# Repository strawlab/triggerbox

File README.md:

# triggerbox - camera triggering for synchronized multi-camera setups

## Principle of operation

Cameras trigger inputs are connected to pin D9 on an Arduino. (Optionally, a
buffer amplifier can be used. See below for why this may be a good idea.) This
is used to generate a digital pulse which triggers image acquisition on cameras.
Furthermore, a host PC communicates with the Arduino to build a live model of
the clocks on both systems and allows very precise (sub-millisecond)
determination of the timing of trigger pulses from the Arduino. This allows
precise timing information to be taken from the resulting acquired image frames.

## Required hardware:

The minimal required hardware is this:

 - Arduino Nano A000005 (later models WILL NOT WORK).

If using the minimal hardware, you will need to connect pin D9 to the trigger
inputs of your camera directly.

## Optional buffer amplified and circuit board:

For additional robustness for multi-camera setups, particularly those that have
an opto-coupled trigger input which accordingly draws substantially more
current, you will want a buffer amplifier to trigger more cameras. In the
`hardware_v1` and `hardware_v2` directories are the PCB layouts, schematics, and enclosure of the triggerbox.
- Hardware_v1: BNC outputs for triggering only
- Hardware_v2: 4-pin terminal block ouputs for triggering and powering the cameras via external powersource.

## Firmware Build and Install

This firmware can be compiled and installed with the Arduino IDE or at
the command line.

### Option 1: Compiling and Uploading using the Arduino IDE

The file `triggerbox.ino` can be opened directly in the [Arduino
IDE](http://arduino.cc/en/main/software). Set your board to Arduino Nano
("Tools"->"Board"->"Arduino Nano"). Set your port ("Tools"->"Port") correctly,
which depends on your specific computer setup. Then click the "Upload" button.

### Option 2: Command-line Compiling and Uploading using Arduino CLI

To build this firmware for an Arduino Nano on Ubuntu linux, do the following
steps.

Install the required software:

Intall [Arduino CLI](https://arduino.github.io/arduino-cli/latest/), then:

    arduino-cli core update-index
    arduino-cli core install arduino:avr

Compile the firmware

    arduino-cli compile --fqbn arduino:avr:nano

Upload the firmware

    # Note the port `/dev/ttyUSB0` may be different on your computer. In Windows,
    # it will be something like `COM4`.
    arduino-cli upload --port /dev/ttyUSB0 --fqbn arduino:avr:nano

## Testing with host PC

Run the standalone demo program on your host PC. 

 * Prerequisite 1: install [rust](https://rustup.rs/).
 * Prerequisite 2 (linux only): make sure you are in the `dialout` group (or
   whichever group owns the device file - `/dev/ttyUSB0` in the example below):
   ```sudo adduser `whoami` dialout```. 

The demo can be run like this:

    cd braid-triggerbox-rs
    # You may need to change the device path from `/dev/ttyUSB0` in this example.
    # On Windows, this will be something like `COM4` instead of `/dev/ttyUSB0`.
    cargo run -- --device /dev/ttyUSB0 --fps 100
    
If successful, the output will look like:

```
Requested 100 fps, using 100 fps
Connecting to trigger device ..
got new time model: None
.. connected.
got new time model: Some(ClockModel { gain: 0.009991053259000182, offset: 1642089273.653188, residuals: 0.00008373855939680652, n_measurements: 5 })
got new time model: Some(ClockModel { gain: 0.009990740683861077, offset: 1642089273.65347, residuals: 0.00008408054048913982, n_measurements: 6 })
got new time model: Some(ClockModel { gain: 0.009990941849537194, offset: 1642089273.6532729, residuals: 0.00008470585419217969, n_measurements: 7 })
got new time model: Some(ClockModel { gain: 0.0099910874851048, offset: 1642089273.6531227, residuals: 0.00008554253827242064, n_measurements: 8 })
got new time model: Some(ClockModel { gain: 0.009991202969104052, offset: 1642089273.652988, residuals: 0.0000863512614728279, n_measurements: 9 })
got new time model: Some(ClockModel { gain: 0.009991223458200693, offset: 1642089273.652963, residuals: 0.00008639545796995662, n_measurements: 10 })
got new time model: Some(ClockModel { gain: 0.009991292201448232, offset: 1642089273.6528616, residuals: 0.00008692377247143668, n_measurements: 11 })
got new time model: Some(ClockModel { gain: 0.009991496510338038, offset: 1642089273.6525416, residuals: 0.00009343214287582668, n_measurements: 12 })
```

## License

Apache 2.0 or MIT at your choice. See `LICENSE-APACHE` and `LICENSE-MIT`.

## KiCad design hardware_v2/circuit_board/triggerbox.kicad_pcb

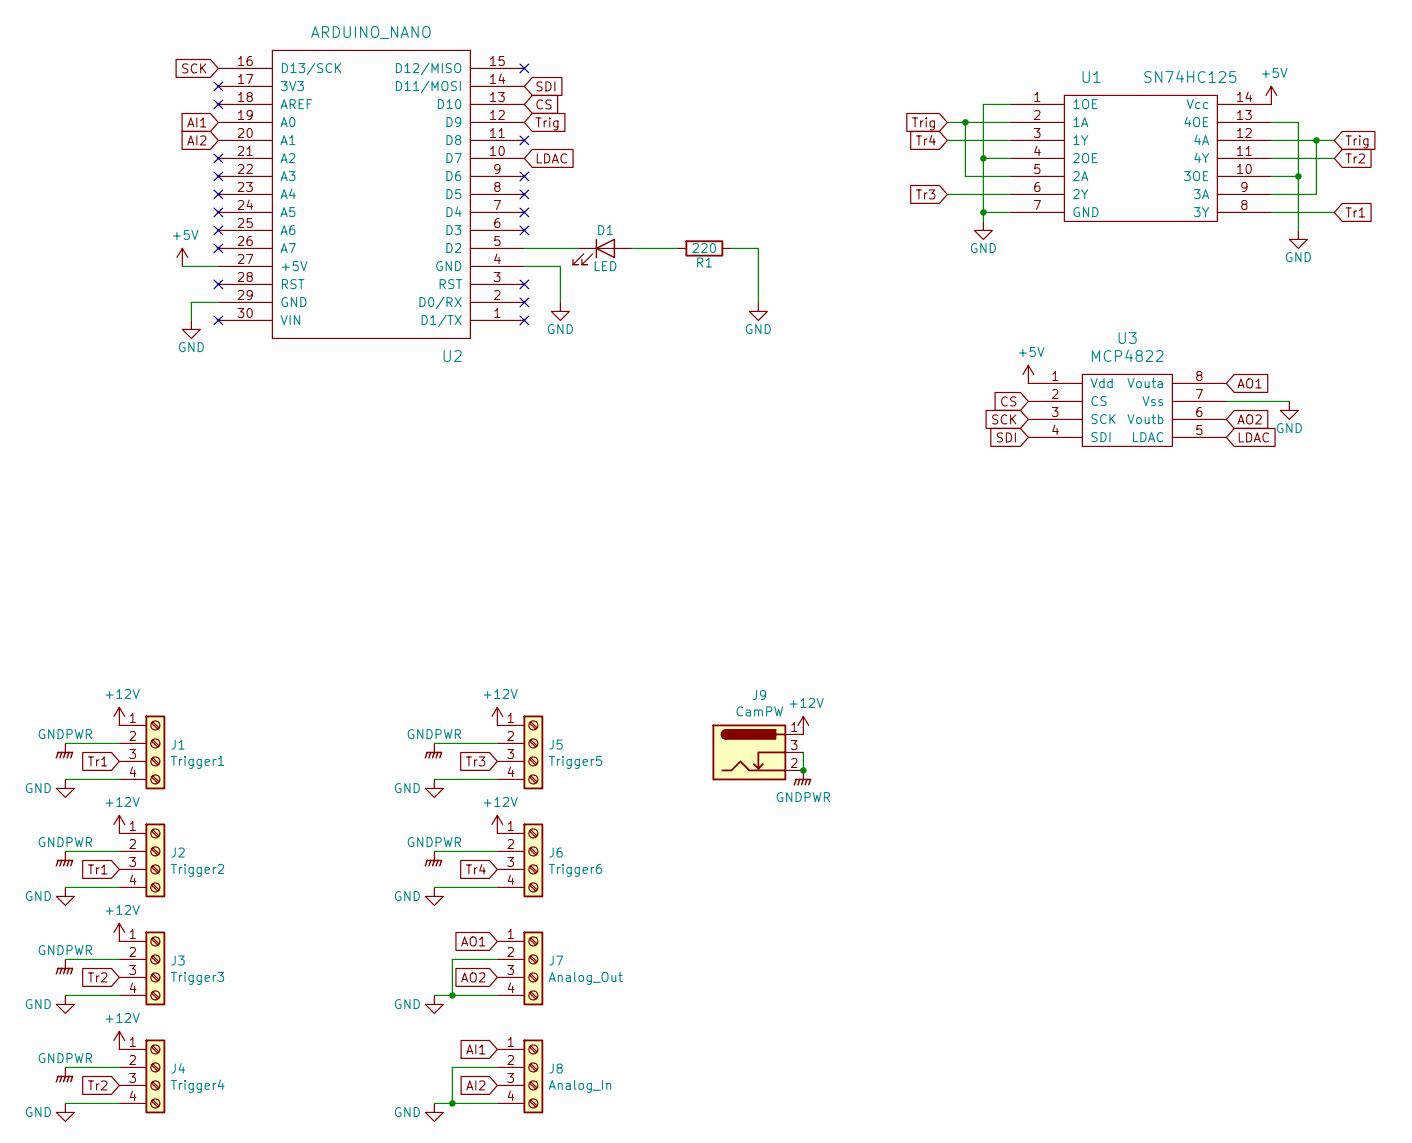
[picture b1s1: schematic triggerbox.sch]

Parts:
D1: LED; LED_0603_1608Metric
J1: Trigger1; TerminalBlock_bornier-4_P5.08mm
J2: Trigger2; TerminalBlock_bornier-4_P5.08mm
J3: Trigger3; TerminalBlock_bornier-4_P5.08mm
J4: Trigger4; TerminalBlock_bornier-4_P5.08mm
J5: Trigger5; TerminalBlock_bornier-4_P5.08mm
J6: Trigger6; TerminalBlock_bornier-4_P5.08mm
J7: Analog_Out; TerminalBlock_bornier-4_P5.08mm
J8: Analog_In; TerminalBlock_bornier-4_P5.08mm
J9: CamPW; BarrelJack_Horizontal
R1: 220; R_0603_1608Metric_Pad1.05x0.95mm_HandSolder
U1: SN74HC125; SOIC-14_3.9x8.7mm_P1.27mm
U2: ARDUINO_NANO; Arduino_Nano
U3: MCP4822; SOIC-8-1EP_3.9x4.9mm_P1.27mm_EP2.29x3mm

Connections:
+5V: U1.14 (Vcc), U2.27 (+5V), U3.1 (Vdd)
+12V: J1.1, J2.1, J3.1, J4.1, J5.1, J6.1, J9.1
AI1: J8.1, U2.19 (A0)
AI2: J8.3, U2.20 (A1)
AO1: J7.1, U3.8 (Vouta)
AO2: J7.3, U3.6 (Voutb)
CS: U2.13 (D10), U3.2 (CS)
GND: J1.4, J2.4, J3.4, J4.4, J5.4, J6.4, J7.2, J7.4, J8.2, J8.4, R1.1, U1.1 (1OE), U1.4 (2OE), U1.7 (GND), U1.10 (3OE), U1.13 (4OE), U2.4 (GND), U2.29 (GND), U3.7 (Vss)
GNDPWR: J1.2, J2.2, J3.2, J4.2, J5.2, J6.2, J9.2, J9.3
LDAC: U2.10 (D7), U3.5 (LDAC)
unnamed: D1.1 (K), U2.5 (D2)
unnamed: D1.2 (A), R1.2
SCK: U2.16 (D13/SCK), U3.3 (SCK)
SDI: U2.14 (D11/MOSI), U3.4 (SDI)
Tr1: J1.3, J2.3, U1.8 (3Y)
Tr2: J3.3, J4.3, U1.11 (4Y)
Tr3: J5.3, U1.6 (2Y)
Tr4: J6.3, U1.3 (1Y)
Trig: U1.2 (1A), U1.5 (2A), U1.9 (3A), U1.12 (4A), U2.12 (D9)

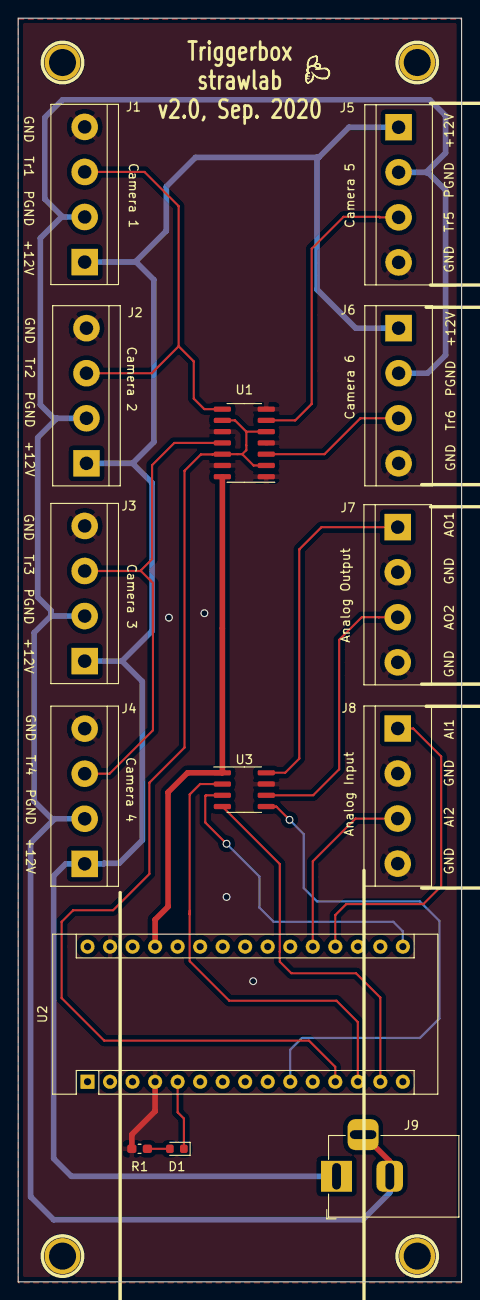
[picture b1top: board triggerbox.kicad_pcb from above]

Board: 2 copper layers, 50.0 x 142.5 mm, 18 parts (0 on the bottom side), 19 nets.

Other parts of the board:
1PIN 1: 1; 1pin
1PIN 2: 2; 1pin
1PIN 3: 3; 1pin
1PIN 4: 4; 1pin

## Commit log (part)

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2013-09-06 firmware: update Makefile and documentation
2013-09-06 ignore built files
2013-09-06 include IORodeo's MCP4822 library
2013-09-06 firmware: use AOUT
2013-09-06 firmware: simplify reading of new ICR1 from serial
2013-09-06 firmware: cleanup pin assignments
2013-09-06 initial support for setting AOUT via ROS
2013-09-06 accept larger errors when fitting time model (stops so many warnings)
2013-09-07 add direct voltage specification output
2013-09-09 add Fritzing file
2013-09-11 ensure channel name is actually connected
2013-09-11 firmware: makefile defaults to Arduino Nano v3
2013-09-13 firmware: default to Nano328
2013-09-17 implement new topic 'pause_and_reset'
2013-09-17 allow slow framerates (< 30 fps)
2013-09-17 don't pause when switching rate
2013-09-17 prevent race condition on startup. emit expected triggerrate.
2013-09-17 add client code
2013-12-01 KiCad files
2013-12-01 annotate schematic
2013-12-01 add png files with parameters
2013-12-01 move params PNGs from gerber dir
2013-12-01 as uploaded to silver circuits
2013-12-02 updates (not uploaded yet)
2013-12-19 add Makefile and accessory files
2013-12-20 convert svg to pdf
2013-12-20 remove outdated unused Fritzing model
2013-12-20 remove redundant code
2013-12-20 enclosure revision
2013-12-20 enclosure: closer to production
2014-01-20 printed attempt 1
2014-01-20 printed attempt 2
2014-01-27 the default host name is triggerbox_host
2014-01-27 script to set the framerate for a triggerbox_host
2014-01-27 gitignores
2014-01-29 more logging
2014-01-29 triggerbox_client: spin until a clockmodel is obtained
2014-01-30 split the triggerbox API so it can be run in-process
2014-01-30 namespace logging
2014-02-07 firmware: stop_pulses command when FPS is 0
2014-02-07 hack backwards compatibility with old trigger stuff
2014-02-07 more robust waiting for time model
2014-02-12 copy files
2014-02-12 update for print v3
2014-02-13 publish raw clock measurements
2014-02-13 publish raw clock measurements (fixes)
2014-04-03 implement a blocking set_framerate service
2014-04-04 refactor common API to be more explicit and callback based
2014-04-04 firmware: start at 25fps
2014-04-04 device: start at 25fps
2014-04-04 api: expose expected_frametate (for set-framerate node)
2014-04-04 bugfix
2014-04-04 add raw_measurement support
2014-04-04 more robust startup. clients should use use set_frames_per_second_blocking at init
2014-04-04 robustness fixes
2014-04-04 set-framerate: use _blocking
2014-04-04 namespace ROS topics when in-process
2014-04-08 more debug printing
2014-04-08 fix synchronize error - rm old cruft
2014-04-28 fix typo
2014-04-28 add set_aout_ab_volts() to API
2014-04-28 add CLI client for triggerbox
2014-04-28 bugfix: triggerbox_client: actually send desired AOUT values
2014-04-28 triggerbox_client: setting AOUT works despite pub/sub race
2014-04-28 triggerbox_host: log ROS subscriber calls
2014-04-29 AOUT: allow output confirmation
2014-05-06 firmware: add rosdep for building firmware
2014-05-07 triggerbox_host: stanalone host can set framerate at startup
    client or inprocess users are expected to do similarly
    themselves
2014-05-07 latch expected framerate publisher
2014-06-24 triggerbox_device: fix AOUT
2014-11-06 triggerbox_device: use arduino-udev
    this is a generalisation of the set-name and
    named concept of the triggerbox, but with an additional
    udev rule that symlinks the named device into
    /dev/
2014-11-07 triggerbox_device: use new udev API
2014-11-07 remove channel-name support
    this is now supported by arduino-udev creating
    device symlinks
2014-12-16 triggerbox_device: fix race at startup
2015-04-01 triggerbox_device: tidy port opening code
2015-04-01 triggerbox_device: try version check multiple times
2015-04-08 triggerbox_device: use new arduino-udev api
2015-04-08 triggerbox_device: try version query a few more times, not time computions
2015-04-08 triggerbox_device: demo supports other ports
2015-04-10 triggerbox_device: block for 5s
2015-04-10 triggerbox_device: debugging print in hex
2015-05-08 firmware: prefer /dev/trig1 for programming
2015-06-06 Convert to ROS Catkin build system
2016-11-27 convert from rosbuild to catkin
2016-12-03 further catkin-ization
2017-07-07 add PDF of schematic
2017-07-17 update to async rospy message sending
2017-12-04 makefile for Arduino uno
2017-12-04 rename makefile to be nano specific
2017-12-04 update readme for nano and uno makefiles
2018-01-04 increase error tolerance in individual timestamp samples
    It seems rather rare for a round-trip time to be less than 15 msec,
    which therefore resulted in long delays before enough samples
    accumulated to allow any estimation of the relative clock rates. By
    increasing the allowed error, we make a clock model sooner.
2018-01-28 bugfix: arduino.mk fails when not using default Makefile name
    This fixes #4.
2018-03-24 add troubleshooting information to the readme
2019-01-17 arudino-udev package is also required
2019-05-10 add rendered versions of the enclosure model
2019-05-10 add svg render
2021-08-01 CI test
2021-08-01 reformat triggerbox.ino
2021-08-05 support only Arduino Nano A000005
2021-08-05 remove ROS support
2021-08-05 python 3 compat
2021-08-05 include UDEV library in Arduino source
    Also, github CI only tests build, does not package hex file.
2021-08-05 simplify repo layout and build instructions
2021-08-05 remove unused dir and files
2021-08-13 remove unmaintained python code
2021-08-13 add license
2021-08-13 update readme to use rust standalone demo
2021-08-13 update dependencies
2021-08-13 update serialport crate
2021-08-13 bugfix: ensure all bytes are written
2021-08-13 clippy fixes
2021-08-13 CI test of rust code
2021-08-13 request dependabot PRs
2021-10-13 return actual trigger rate
2021-10-13 braid-triggerbox-rs 2.0
2021-10-13 make max measurement error configurable
2021-10-13 extract fit_time_model() function and test it
2021-10-17 braid-triggerbox-rs 0.2.1
2021-12-07 add --max-time-error-msec CLI option
2021-12-07 add triggerbox design with terminal block ouputs
2022-01-03 Update nalgebra requirement from 0.29 to 0.30 in /braid-triggerbox-rs
    Updates the requirements on [nalgebra](https://github.com/dimforge/nalgebra) to permit the latest version.
    - [Release notes](https://github.com/dimforge/nalgebra/releases)
    - [Changelog](https://github.com/dimforge/nalgebra/blob/dev/CHANGELOG.md)
    - [Commits](https://github.com/dimforge/nalgebra/compare/v0.29.0...v0.30.0)
    ---
    updated-dependencies:
2022-01-03 Update lstsq requirement from 0.2 to 0.3 in /braid-triggerbox-rs
    Updates the requirements on [lstsq](https://github.com/strawlab/lstsq) to permit the latest version.
    - [Release notes](https://github.com/strawlab/lstsq/releases)
    - [Commits](https://github.com/strawlab/lstsq/compare/0.2.0...0.3.0)
    ---
    updated-dependencies:
    - dependency-name: lstsq
2022-01-04 release 0.2.2
2022-01-13 in linux, the user should be in the dialout group
2022-02-09 better version check error
2022-02-09 test crc
2022-02-09 use crc crate
2022-03-17 use normal rust panic handling
2022-03-18 use published braid-triggerbox-comms crate
2022-03-18 better naming
2022-03-18 explicitly show device name string
2022-03-18 release 0.2.3
2022-03-18 make async. use tokio-serial instead of serialport
2022-03-18 release 0.3.0
2022-03-20 timeout when waiting for device
2022-03-20 clippy fix
2022-03-20 cleanups
2022-03-20 5 sec timeout
2022-03-20 release 0.3.1
2022-03-22 compatibility fixes
    Fix for Arduino Nano based hardware. Also refactor and expose new API.
2022-03-22 bump tokio-serial version
2022-03-22 add comment
2022-03-22 fix behavior when waiting for version number
2022-03-23 release 0.3.3
2022-03-23 release 0.3.4
2022-05-02 Update nalgebra requirement from 0.30 to 0.31 in /braid-triggerbox-rs
    Updates the requirements on [nalgebra](https://github.com/dimforge/nalgebra) to permit the latest version.
    - [Release notes](https://github.com/dimforge/nalgebra/releases)
    - [Changelog](https://github.com/dimforge/nalgebra/blob/dev/CHANGELOG.md)
    - [Commits](https://github.com/dimforge/nalgebra/compare/v0.30.0...v0.31.0)
    ---
    updated-dependencies:
2022-05-02 Update crc requirement from 2.1 to 3.0 in /braid-triggerbox-rs
    Updates the requirements on [crc](https://github.com/mrhooray/crc-rs) to permit the latest version.
    - [Release notes](https://github.com/mrhooray/crc-rs/releases)
    - [Commits](https://github.com/mrhooray/crc-rs/compare/2.1.0...3.0.0)
    ---
    updated-dependencies:
    - dependency-name: crc
2022-05-02 release 0.3.5
2022-08-02 braid-triggerbox-firmware-pico initial commit
2022-08-02 build firmware using github actions
    This also consolidates github actions to single .yml file.
2022-11-03 braid-triggerbox-demo: add '--run-mode stop' CLI option.
2022-11-04 braid-triggerbox-demo: actually keep trigger stopped
2022-11-25 Update env_logger requirement from 0.9 to 0.10 in /braid-triggerbox-rs
    Updates the requirements on [env_logger](https://github.com/rust-cli/env_logger) to permit the latest version.
    - [Release notes](https://github.com/rust-cli/env_logger/releases)
    - [Changelog](https://github.com/rust-cli/env_logger/blob/main/CHANGELOG.md)
    - [Commits](https://github.com/rust-cli/env_logger/compare/v0.9.0...v0.10.0)
    ---
    updated-dependencies:
2022-12-16 braid-triggerbox-rs: remove non-backwards compatible firmware
    It was a mistake to include new features only on the Pico-based hardware.
2022-12-16 remove redundant crate
2022-12-16 braid-triggerbox-comms: add test encode/decode tests for all message types
2022-12-16 braid-triggerbox-firmware-pico: update rp-pico 0.2.0 -> 0.6.0
2022-12-16 braid-triggerbox-firmware-pico: update dependencies
2022-12-16 braid-triggerbox-firmware-pico: bugfix: many interrupted messages
2022-12-16 CI also runs weekly
2022-12-16 CI: run latest OSes
2022-12-16 CI: test multiple OS
2022-12-16 braid-triggerbox-rs: slight simplification and tweaks for nano
    The Arduino Nano (https://content.arduino.cc/assets/NanoV3.3_sch.pdf) has
    no connection to the RTS line so we can safely remove the calls that set it.
    The rest of the changes here were tried emperically on an old Nano.
2023-01-11 do not depend on time 0.1
2023-01-16 Update nalgebra requirement from 0.31 to 0.32 in /braid-triggerbox-rs
    Updates the requirements on [nalgebra](https://github.com/dimforge/nalgebra) to permit the latest version.
    - [Release notes](https://github.com/dimforge/nalgebra/releases)
    - [Changelog](https://github.com/dimforge/nalgebra/blob/dev/CHANGELOG.md)
    - [Commits](https://github.com/dimforge/nalgebra/compare/v0.31.0...v0.32.1)
    ---
    updated-dependencies:
2023-01-16 complete update to nalgebra 0.32
2023-02-03 run 'cargo clippy --fix' with rust 1.67
2023-02-03 cargo clippy fix
2023-05-07 CI: use dtolnay/rust-toolchain
2023-05-07 CI: install elf2uf2-rs --locked
2023-05-19 CI workaround broken dependencies
    See:
    * https://github.com/JoNil/elf2uf2-rs/issues/17
    * https://github.com/JoNil/elf2uf2-rs/pull/19
2023-05-19 CI remove actions-rs dependency
2023-05-19 CI bump to github action arduino/setup-arduino-cli@v1.1.2
2023-05-19 CI use github action actions/checkout@v3
2023-05-19 CI remove unused checks
    I think these were never run and we check the hardware_v3 firmware in the main
    `ci.yml` file.
2023-11-11 move clock emulation code
    We emulate the Nano PWM clock on the Pico. Move that code to a library
    crate to simplify the specific pico code.
2023-11-11 update heapless dep
2023-11-11 update rp-pico dep
2023-11-11 make some assertions compile-time
2023-11-11 flexible clock freq
2023-11-11 cleanup
2023-11-11 add docstrings
2024-01-22 Update env_logger requirement from 0.10 to 0.11 in /braid-triggerbox-rs
    Updates the requirements on [env_logger](https://github.com/rust-cli/env_logger) to permit the latest version.
    - [Release notes](https://github.com/rust-cli/env_logger/releases)
    - [Changelog](https://github.com/rust-cli/env_logger/blob/main/CHANGELOG.md)
    - [Commits](https://github.com/rust-cli/env_logger/compare/v0.10.0...v0.11.0)
    ---
    updated-dependencies:
2024-10-26 braid-triggerbox-rs: update dependencies
